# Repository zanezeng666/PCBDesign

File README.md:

# Battery Protection Board Designer

本地参数化电池保护板设计服务。系统将照片轮廓、触点角色、电池参数和版本化 IC 器件包转换为机械预览，并在存在审核过的 KiCad 模板时生成候选样板生产文件。

## 启动

```powershell
& "C:\Users\26509\.cache\codex-runtimes\codex-primary-runtime\dependencies\python\python.exe" -m venv .venv
& .\.venv\Scripts\python.exe -m pip install -r requirements.txt
& .\.venv\Scripts\python.exe -m pip install --no-deps -r requirements-ocr.txt
.\run.ps1
```

打开 `http://127.0.0.1:8000`。健康检查位于 `/api/health`，API 文档位于 `/docs`。

## 正反面照片

- 正面照片建立 PCB 的统一毫米坐标系。
- 对没有标记的历史照片，可输入已确认的矩形板框宽高。系统优先识别四个可见板角并执行单应性透视矫正；板角不可靠时回退为旋转矩形裁切，并在界面明确提示。该模式必须人工确认，不能宣称达到 ArUco 模式的 0.2 mm 精度。
- 反面照片单独完成 ArUco 标定，然后选择左右翻转、上下翻转或旋转 180°映射到正面坐标。
- 正反面轮廓平均对齐误差不超过 0.2 mm 为良好，0.2～0.5 mm 必须人工仔细确认，超过 0.5 mm 拒绝创建项目。
- 每个触点保存 `front/back` 板面；反面触点必须存在对应的背面标定记录。
- `TH`、`ID` 等辅助信号可保存为无极性触点，但仅凭丝印不会自动推断其内部网络。
- “自动识别当前面”先识别有限标签集 `B+ / B- / P+ / P- / C+ / C- / NTC / N / TH / ID`，再按文字框边缘距离匹配最近的银白色焊盘区域或孔位。候选保存文字框、区域轮廓、外接矩形、中心、尺寸、区域类型和匹配距离；没有匹配到实体区域的文字不能采纳。低置信度误读会保留原始识别文本供复核。
- 原始照片、校正图和标定结果会随项目保存，便于审计。

## 安全边界

- 只接受 1～5 颗纯串联或纯并联。
- 共口/分口由同一个触点是否同时具备充电和放电角色推导。
- 未验证 IC 始终标记为 `candidate`。
- 机械预览不代表电气设计完成。
- 生产输出必须有版本化 KiCad 模板、模板适配器，并通过 ERC、DRC 和零未连接门禁。
- 不存在空 PCB、静默丢线或失败后继续导出的降级路径。

## IC 自动解析

内置目录位于 `data/ic_catalog`。未知型号通过环境变量 `IC_RESOLVER_ENDPOINT` 指定的结构化解析服务检索；解析服务应返回按官方资料提取的候选 JSON。系统确定性排序并自动使用第一项，缓存原始结果和来源。无法得到完整引脚、封装、串数及端口拓扑时会失败。

Fortune Semiconductor 的 DW01-G 当前只登记为元数据候选，尚未绑定可信 KiCad 模板，因此可以完成输入检查与机械预览，但不会伪造 Gerber。

## 测试

```powershell
& .\.venv\Scripts\python.exe -m pytest
```

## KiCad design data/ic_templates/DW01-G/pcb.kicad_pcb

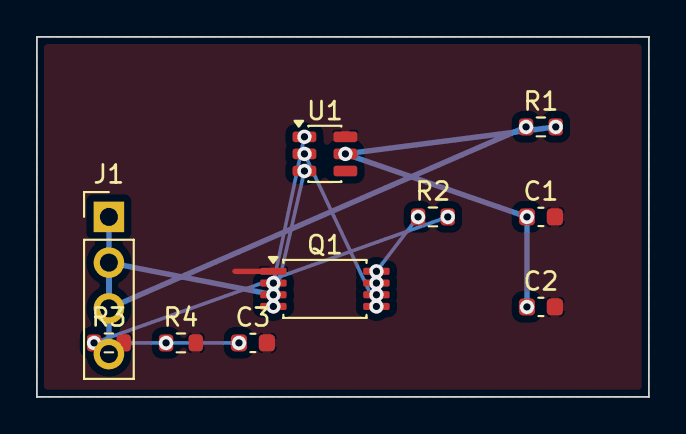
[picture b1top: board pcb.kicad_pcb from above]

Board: 2 copper layers, 34.0 x 20.0 mm, 10 parts (0 on the bottom side), 8 nets.

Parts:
C1, C2, C3: C_0603_1608Metric
J1: PinHeader_1x04_P2.54mm_Vertical
Q1: TSSOP-8_4.4x3mm_P0.65mm
R1, R2, R3, R4: R_0603_1608Metric
U1: SOT-23-6

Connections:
B+: J1.1, J1.3, R1.1
B-: C1.2, C2.2, C3.2, Q1.1, R3.2, R4.2, U1.6
MID: Q1.5, Q1.6, Q1.7, Q1.8, R2.1, U1.2
OC: Q1.4, U1.3
OD: Q1.2, U1.1
P-: J1.2, J1.4, Q1.3
TH: C3.1, R2.2, R3.1
VDD: C1.1, C2.1, R1.2, U1.5
